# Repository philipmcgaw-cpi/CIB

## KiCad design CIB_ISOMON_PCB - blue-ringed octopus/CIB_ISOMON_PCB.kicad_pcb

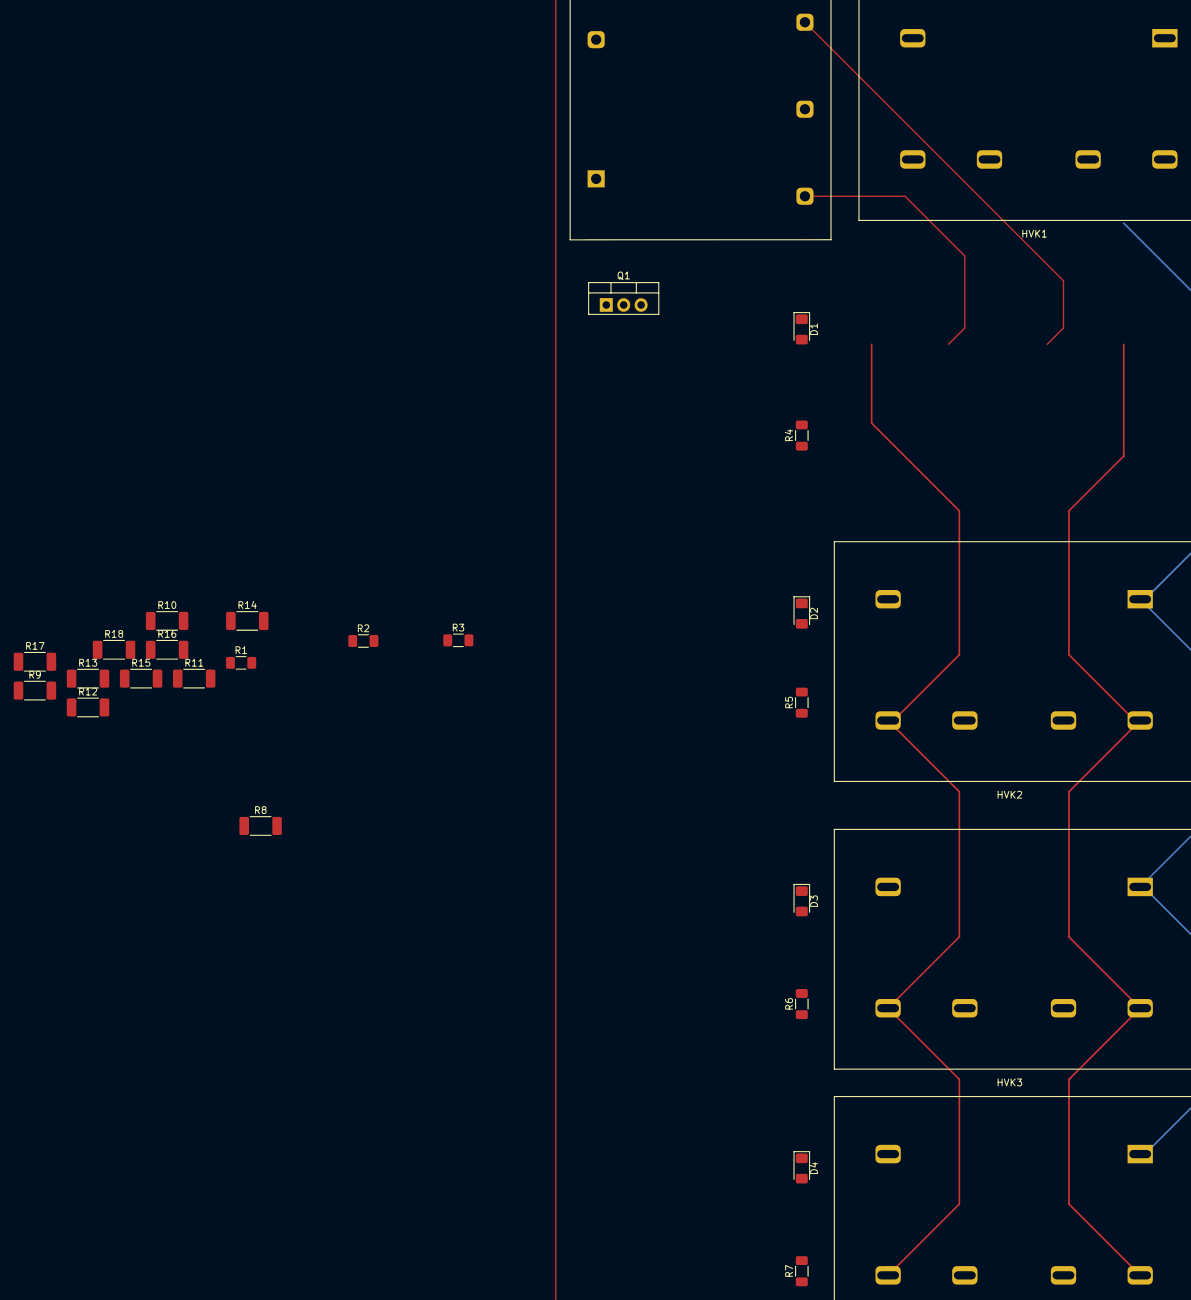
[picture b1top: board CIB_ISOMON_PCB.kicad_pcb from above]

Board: 2 copper layers, 28 parts (0 on the bottom side), 25 nets.

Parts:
D1, D2, D3, D4: Red; D_1206_3216Metric_Pad1.42x1.75mm_HandSolder
HVK1, HVK2, HVK3: G7L-2A-X_DC12
HVK4: Connectors:G7L-2A-X_DC12; G7L-2A-X_DC12
PSU1: DC-HVDC_G10; DC-HVDC Converter G10
Q1: TIP127; TO-220-3_Vertical
R1, R2, R3: 470; R_1206_3216Metric_Pad1.30x1.75mm_HandSolder
R4, R5, R6, R7: 1k2; R_1206_3216Metric_Pad1.30x1.75mm_HandSolder
R8, R9, R10, R11, R12, R14, R15, R16, R17, R18: 1M; R_2010_5025Metric_Pad1.40x2.65mm_HandSolder
R13: 0; R_2010_5025Metric_Pad1.40x2.65mm_HandSolder

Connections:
+12V: HVK1.0, HVK2.0, HVK3.0, HVK4.0, Q1.2 (C), R4.1, R5.1, R6.1, R7.1
/HV ISOMON +VE: HVK1.8, HVK2.8, HVK3.8, HVK4.8, R8.1
/HV ISOMON -VE: HVK1.2, HVK2.2, HVK3.2, HVK4.2, R14.1
/HV PSU +Ve: PSU1.1 (+Vin), Q1.3 (E), R3.1
/HV PSU OP+: HVK1.6, PSU1.3 (+Vout)
/HV PSU OP-: HVK1.4, PSU1.4 (-Vout)
/HVK1: D1.1 (K), HVK1.1
/HVK2: D2.1 (K), HVK2.1
/HVK3: D3.1 (K), HVK3.1
/HVK4: D4.1 (K), HVK4.1
GND: PSU1.2 (-Vin), PSU1.5 (0V), R2.2, R3.2, R13.2
unnamed: D1.2 (A), R4.2
unnamed: D2.2 (A), R5.2
unnamed: D3.2 (A), R6.2
unnamed: D4.2 (A), R7.2
unnamed: R1.1, R2.1
unnamed: R8.2, R9.1
unnamed: R9.2, R10.1
unnamed: R10.2, R11.1
unnamed: R11.2, R12.1
unnamed: R12.2, R13.1, R18.2
unnamed: R14.2, R15.1
unnamed: R15.2, R16.1
unnamed: R16.2, R17.1
unnamed: R17.2, R18.1

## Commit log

2022-06-27 start
2022-06-27 deletions
2022-06-28 added snubbing to the relays
2022-06-28 named folders with animal names
2022-06-29 Added revision resistors
2022-06-30 added version resistors
2022-07-04 message
2022-07-05 temp?
2022-07-07 added some librarys
2022-07-07 removed backups
2022-07-07 removed librarys
2022-07-08 cache
2022-07-08 added changes
2022-07-12 V0.1 PCB to be sent out
2022-07-12 working on harness diagram
2022-07-13 Added changes due to error at fab
2022-07-13 Generated Bom, and cleaned up layers.
2022-07-13 export bom csv
